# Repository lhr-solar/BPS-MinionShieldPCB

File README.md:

# BPS-MinionShieldPCB
Author: Champers Fu

This board sits on top of the minionshield to interface with the temperature sensors. 
The board provides a low pass filter between the thermistors and the LTC6811 input. 

## BOM
[**Interactive BOM (Must download and open in browser)**](ibom.html)

[**Mouser Cart**](https://www.mouser.com/ProjectManager/ProjectDetail.aspx?AccessID=0a4c326737)
Note: The PADP-24V-1-S connector is not available on mouser, but may be purchased through [**digikey**](https://www.digikey.com/en/products/detail/jst-sales-america-inc/PADP-24V-1-S/1300227)

## Connectors
| Reference | Name | Type | Pin 1 | 2 | 3 | 4 | 5 | 6 | 7 | 8 | 9 | 10 |
| - | - | - | - | - | - | - | - | - | - | - | - | - |
| J1 | MinionPCB Connector | 1x10xP2.54mm Male | 5V | TempSensor1 | TempSensor2 | TempSensor3 | TempSensor4 | TempSensor5 | TempSensor6 | TempSensor7 | TempSensor8 | GND
| J2 | MinionPCB Connector | 1x10xP2.54mm Male | 5V | TempSensor9 | TempSensor10 | TempSensor11 | TempSensor12 | TempSensor13 | TempSensor14 | TempSensor15 | TempSensor16 | GND
| J3 | Thermistors | PADP-24V-1-S | See Schematic | | | | | | | | | |

## PCB
[**PDF without traces**](PCB.pdf)

## Schematic
[**PDF with all sheets**](Schematic.pdf)

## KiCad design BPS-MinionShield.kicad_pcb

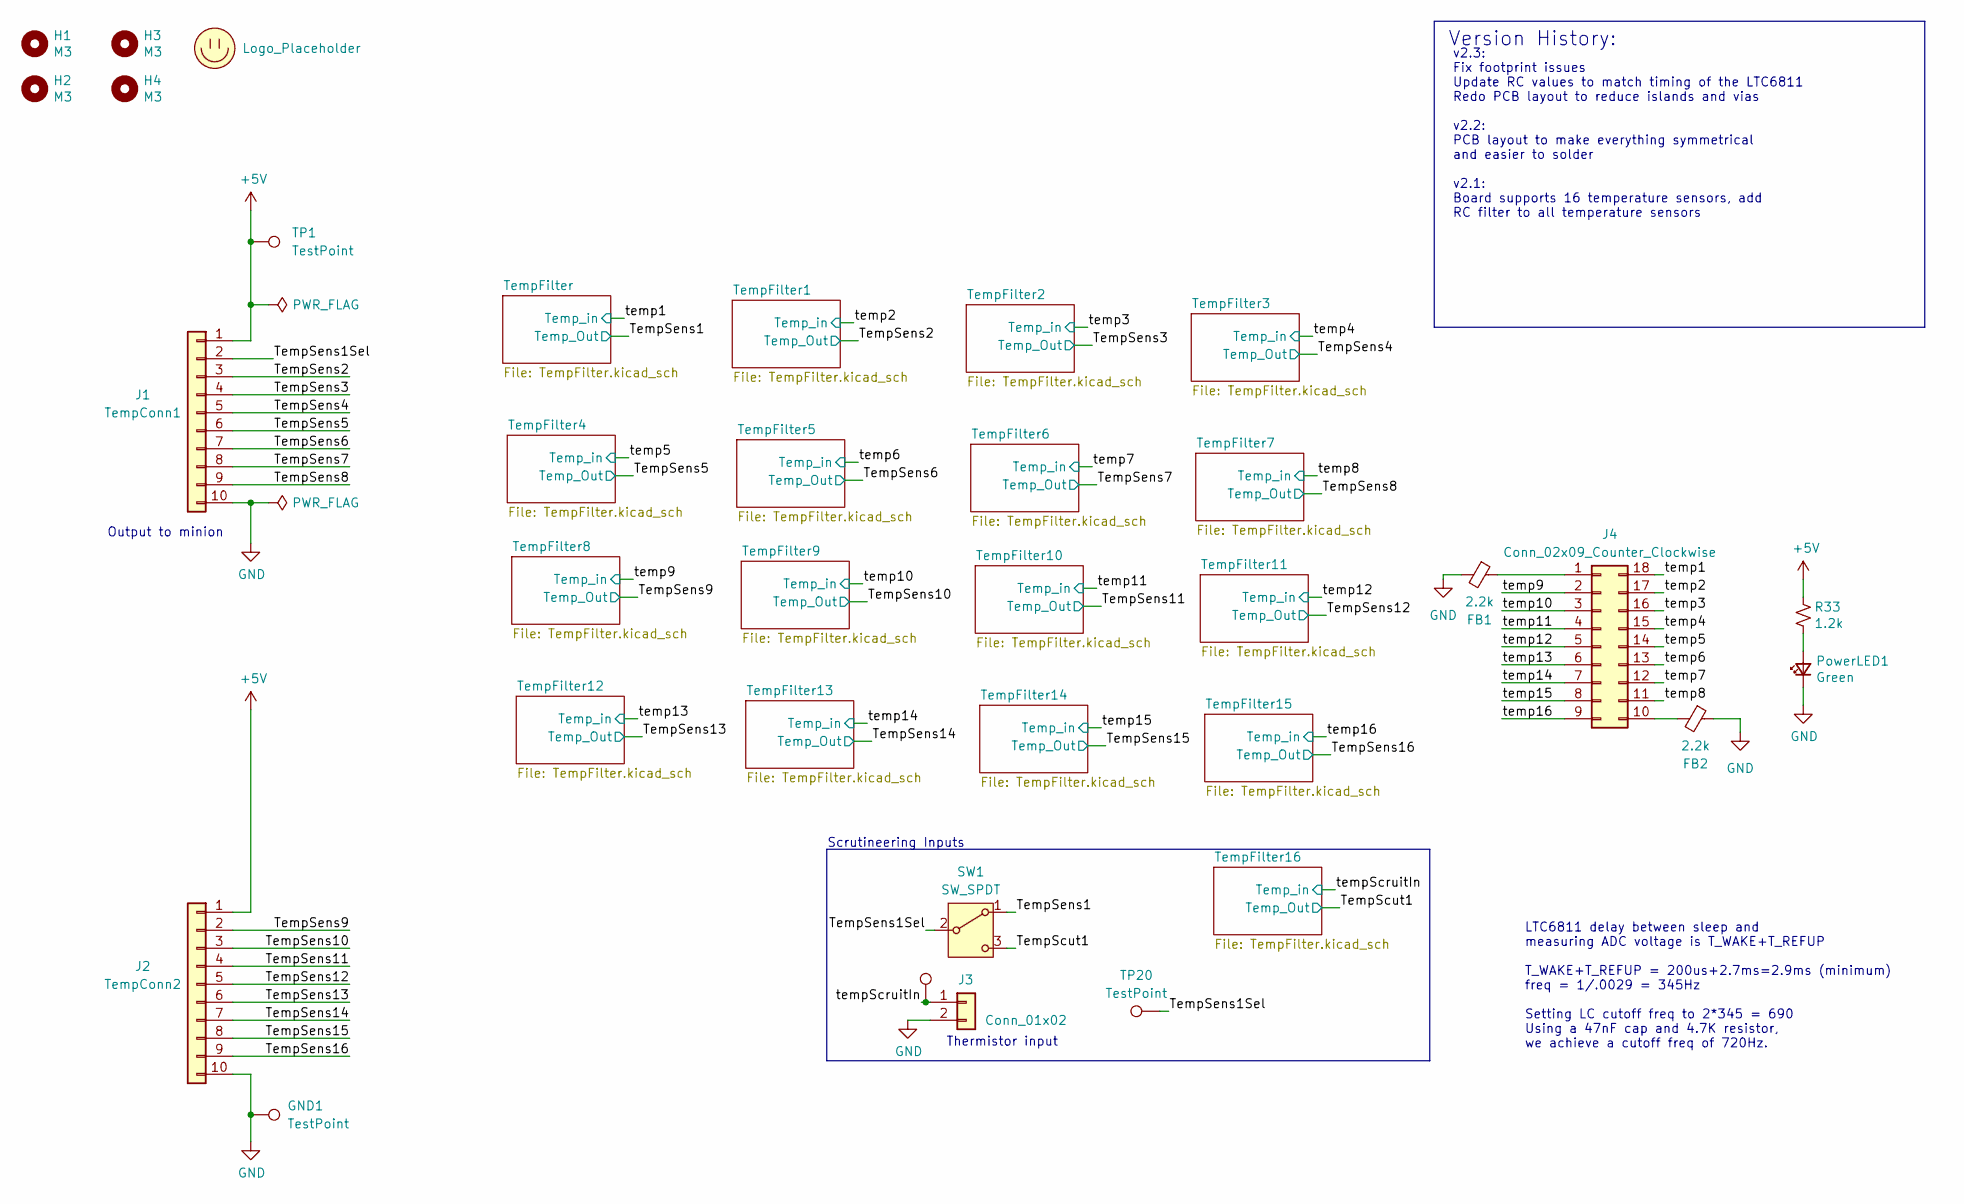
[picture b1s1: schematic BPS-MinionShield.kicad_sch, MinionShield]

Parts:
FB1, FB2: 2.2k; L_0805_2012Metric_Pad1.05x1.20mm_HandSolder
GND1: TestPoint; TestPoint_THTPad_D1.5mm_Drill0.7mm
H1, H2, H3, H4: M3; MountingHole_3mm
J1: TempConn1; PinHeader_1x10_P2.54mm_Vertical
J2: TempConn2; PinHeader_1x10_P2.54mm_Vertical
J3: Conn_01x02; Molex_MicroFit3.0_1x2xP3.00mm_PolarizingPeg_Vertical
J4: Conn_02x09_Counter_Clockwise; Molex_Micro-Fit_3.0_43045-1800_2x09_P3.00mm_Horizontal
LOGO1: Logo_Placeholder; Hallock_Image_Small
PowerLED1: Green; LED_0805_2012Metric_Pad1.15x1.40mm_HandSolder; LCSC Part # C94741
R33: 1.2k; R_0805_2012Metric_Pad1.20x1.40mm_HandSolder; LCSC Part # C17673
SW1: SW_SPDT; CJS1200TB1
TP1, TP2: TestPoint; TestPoint_THTPad_D1.5mm_Drill0.7mm
TP20: TestPoint; TestPoint_Pad_1.5x1.5mm

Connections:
+5V: J1.1, J2.1, R33.1, TP1.1; also elsewhere on the board
/TempScut1: SW1.3 (C); also elsewhere on the board
/TempSens1: SW1.1 (A); also elsewhere on the board
/TempSens1Sel: J1.2, SW1.2 (B), TP20.1
/TempSens2: J1.3; also elsewhere on the board
/TempSens3: J1.4; also elsewhere on the board
/TempSens4: J1.5; also elsewhere on the board
/TempSens5: J1.6; also elsewhere on the board
/TempSens6: J1.7; also elsewhere on the board
/TempSens7: J1.8; also elsewhere on the board
/TempSens8: J1.9; also elsewhere on the board
/TempSens9: J2.2; also elsewhere on the board
/TempSens10: J2.3; also elsewhere on the board
/TempSens11: J2.4; also elsewhere on the board
/TempSens12: J2.5; also elsewhere on the board
/TempSens13: J2.6; also elsewhere on the board
/TempSens14: J2.7; also elsewhere on the board
/TempSens15: J2.8; also elsewhere on the board
/TempSens16: J2.9; also elsewhere on the board
/temp1: J4.18; also elsewhere on the board
/temp2: J4.17; also elsewhere on the board
/temp3: J4.16; also elsewhere on the board
/temp4: J4.15; also elsewhere on the board
/temp5: J4.14; also elsewhere on the board
/temp6: J4.13; also elsewhere on the board
/temp7: J4.12; also elsewhere on the board
/temp8: J4.11; also elsewhere on the board
/temp9: J4.2; also elsewhere on the board
/temp10: J4.3; also elsewhere on the board
/temp11: J4.4; also elsewhere on the board
/temp12: J4.5; also elsewhere on the board
/temp13: J4.6; also elsewhere on the board
/temp14: J4.7; also elsewhere on the board
/temp15: J4.8; also elsewhere on the board
/temp16: J4.9; also elsewhere on the board
/tempScruitIn: J3.1, TP2.1; also elsewhere on the board
GND: FB1.2, FB2.1, GND1.1, J1.10, J2.10, J3.2, PowerLED1.1 (K); also elsewhere on the board
unnamed: FB1.1, J4.1
unnamed: FB2.2, J4.10
unnamed: PowerLED1.2 (A), R33.2

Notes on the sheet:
Thermistor input
Version History:
v2.3: Fix footprint issues Update RC values to match timing of the LTC6811 Redo PCB layout to reduce islands and vias v2.2: PCB layout to make everything symmetrical and easier to solder v2.1: Board supports 16 temperature sensors, add RC filter to all temperature sensors
Scrutineering Inputs
LTC6811 delay between sleep and measuring ADC voltage is T_WAKE+T_REFUP T_WAKE+T_REFUP = 200us+2.7ms=2.9ms (minimum) freq = 1/.0029 = 345Hz Setting LC cutoff freq to 2*345 = 690 Using a 47nF cap and 4.7K resistor, we achieve a cutoff freq of 720Hz.
Output to minion

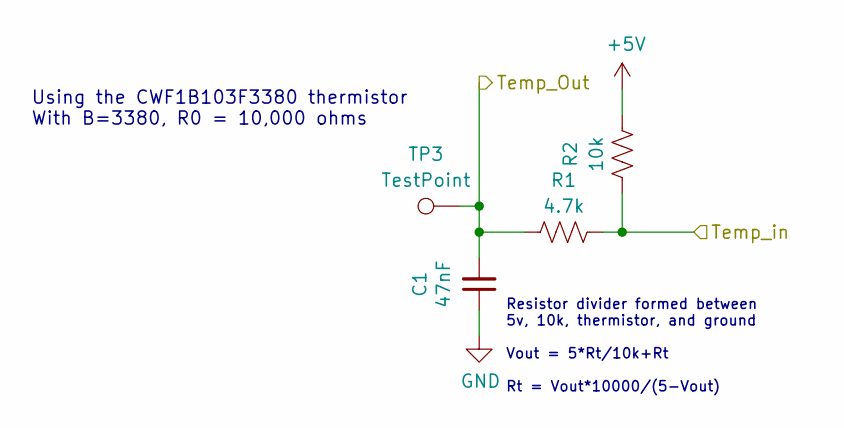
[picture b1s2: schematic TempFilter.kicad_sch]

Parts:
C1: 47nF; C_0805_2012Metric_Pad1.18x1.45mm_HandSolder; LCSC Part # C1745
R1: 4.7k; R_0805_2012Metric_Pad1.20x1.40mm_HandSolder; LCSC Part # C17673
R2: 10k; R_0805_2012Metric_Pad1.20x1.40mm_HandSolder; LCSC Part # C17414
TP3: TestPoint; TestPoint_Pad_1.5x1.5mm

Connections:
+5V: R2.2; also elsewhere on the board
/TempSens1: C1.2, R1.1, TP3.1; also elsewhere on the board
/temp1: R1.2, R2.1; also elsewhere on the board
GND: C1.1; also elsewhere on the board

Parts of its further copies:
C2, C3, C4, C5, C6, C7, C8, C9, C10, C11, C12, C13, C14, C15, C16, C17: 47nF; C_0805_2012Metric_Pad1.18x1.45mm_HandSolder; LCSC Part # C1745
R3, R5, R7, R9, R11, R13, R15, R17, R19, R21, R23, R25, R27, R29, R31, R34: 4.7k; R_0805_2012Metric_Pad1.20x1.40mm_HandSolder; LCSC Part # C17673
R4, R6, R8, R10, R12, R14, R16, R18, R20, R22, R24, R26, R28, R30, R32, R35: 10k; R_0805_2012Metric_Pad1.20x1.40mm_HandSolder; LCSC Part # C17414
TP4, TP5, TP6, TP7, TP8, TP9, TP10, TP11, TP12, TP13, TP14, TP15, TP16, TP17, TP18, TP19: TestPoint; TestPoint_Pad_1.5x1.5mm

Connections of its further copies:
+5V: R4.2, R6.2, R8.2, R10.2, R12.2, R14.2, R16.2, R18.2, R20.2, R22.2, R24.2, R26.2, R28.2, R30.2, R32.2, R35.2; also elsewhere on the board
/TempScut1: C17.2, R34.1, TP19.1; also elsewhere on the board
/TempSens2: C2.2, R3.1, TP4.1; also elsewhere on the board
/TempSens3: C3.2, R5.1, TP5.1; also elsewhere on the board
/TempSens4: C4.2, R7.1, TP6.1; also elsewhere on the board
/TempSens5: C5.2, R9.1, TP7.1; also elsewhere on the board
/TempSens6: C6.2, R11.1, TP8.1; also elsewhere on the board
/TempSens7: C7.2, R13.1, TP9.1; also elsewhere on the board
/TempSens8: C8.2, R15.1, TP10.1; also elsewhere on the board
/TempSens9: C9.2, R17.1, TP11.1; also elsewhere on the board
/TempSens10: C10.2, R19.1, TP12.1; also elsewhere on the board
/TempSens11: C11.2, R21.1, TP13.1; also elsewhere on the board
/TempSens12: C12.2, R23.1, TP14.1; also elsewhere on the board
/TempSens13: C13.2, R25.1, TP15.1; also elsewhere on the board
/TempSens14: C14.2, R27.1, TP16.1; also elsewhere on the board
/TempSens15: C15.2, R29.1, TP17.1; also elsewhere on the board
/TempSens16: C16.2, R31.1, TP18.1; also elsewhere on the board
/temp2: R3.2, R4.1; also elsewhere on the board
/temp3: R5.2, R6.1; also elsewhere on the board
/temp4: R7.2, R8.1; also elsewhere on the board
/temp5: R9.2, R10.1; also elsewhere on the board
/temp6: R11.2, R12.1; also elsewhere on the board
/temp7: R13.2, R14.1; also elsewhere on the board
/temp8: R15.2, R16.1; also elsewhere on the board
/temp9: R17.2, R18.1; also elsewhere on the board
/temp10: R19.2, R20.1; also elsewhere on the board
/temp11: R21.2, R22.1; also elsewhere on the board
/temp12: R23.2, R24.1; also elsewhere on the board
/temp13: R25.2, R26.1; also elsewhere on the board
/temp14: R27.2, R28.1; also elsewhere on the board
/temp15: R29.2, R30.1; also elsewhere on the board
/temp16: R31.2, R32.1; also elsewhere on the board
/tempScruitIn: R34.2, R35.1; also elsewhere on the board
GND: C2.1, C3.1, C4.1, C5.1, C6.1, C7.1, C8.1, C9.1, C10.1, C11.1, C12.1, C13.1, C14.1, C15.1, C16.1, C17.1; also elsewhere on the board

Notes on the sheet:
Using the CWF1B103F3380 thermistor With B=3380, R0 = 10,000 ohms
Resistor divider formed between 5v, 10k, thermistor, and ground Vout = 5*Rt/10k+Rt Rt = Vout*10000/(5-Vout)

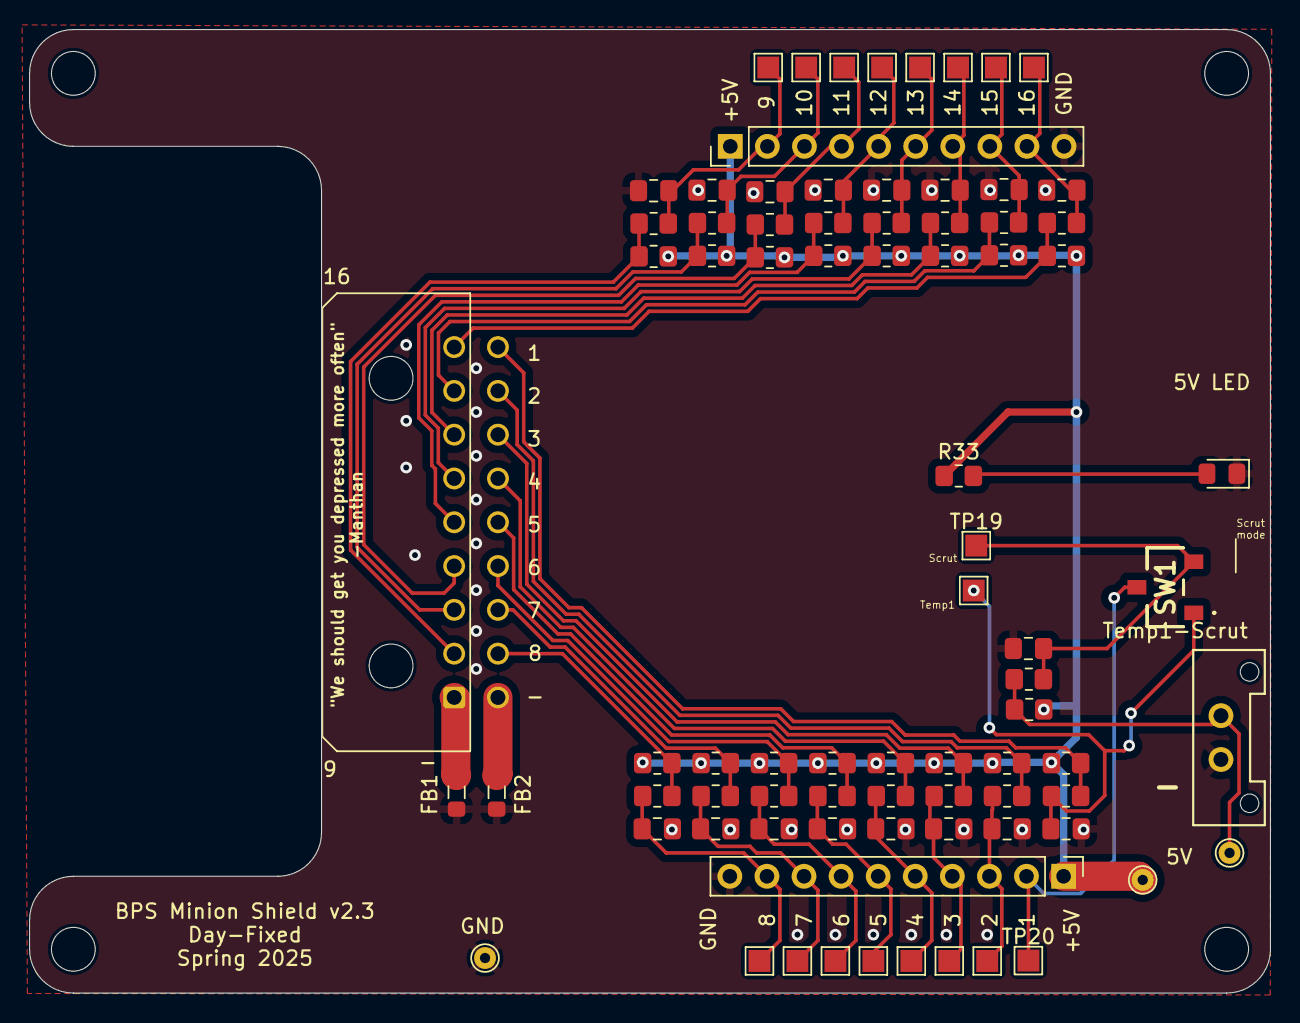
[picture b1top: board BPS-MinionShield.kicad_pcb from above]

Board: 2 copper layers, 85.0 x 66.0 mm, 86 parts (1 on the bottom side), 40 nets.

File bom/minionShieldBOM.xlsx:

Reference | Value | Datasheet | Footprint | Qty | DNP | p/n
C1,C2,C3,C4,C5,C6,C7,C8,C9,C10,C11,C12,C13,C14,C15,C16 | 47nF | https://www.mouser.com/ProductDetail/YAGEO/CC0805JRX7R9BB473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 | Capacitor_SMD:C_0805_2012Metric_Pad1.18x1.45mm_HandSolder | 16 |  | CC0805JRX7R9BB473
FB1,FB2 | 2.2k | https://www.digikey.com/en/products/detail/laird-signal-inte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 | Inductor_SMD:L_0805_2012Metric_Pad1.05x1.20mm_HandSolder | 2 |  | HZ0805B222R-10
J3 | Conn_01x02 | ~ | UTSVT_Connectors:Molex_MicroFit3.0_1x2xP3.00mm_PolarizingPeg_Vertical | 1 |  | 436500227
J4 | Conn_02x09_Counter_Clockwise | ~ | Connector_Molex:Molex_Micro-Fit_3.0_43045-1800_2x09_P3.00mm_Horizontal | 1 |  | 43045-1800
PowerLED1 | Green | https://www.mouser.com/ProductDetail/710-150080VS75000 | LED_SMD:LED_0805_2012Metric_Pad1.15x1.40mm_HandSolder | 1 |  | 150080VS75000
R1,R3,R5,R7,R9,R11,R13,R15,R17,R19,R21,R23,R25,R27,R29,R31 | 4.7k | https://www.mouser.com/ProductDetail/603-RT0805FRE074K7L | Resistor_SMD:R_0805_2012Metric_Pad1.20x1.40mm_HandSolder | 16 |  | RT0805FRE074K7L
R2,R4,R6,R8,R10,R12,R14,R16,R18,R20,R22,R24,R26,R28,R30,R32 | 10k | https://www.mouser.com/ProductDetail/603-RT0805FRE0710KL | Resistor_SMD:R_0805_2012Metric_Pad1.20x1.40mm_HandSolder | 16 |  | RT0805FRE0710KL
R33 | 1.2k | https://www.mouser.com/ProductDetail/603-RT0805FRE071K2L | Resistor_SMD:R_0805_2012Metric_Pad1.20x1.40mm_HandSolder | 1 |  | RT0805FRE071K2L
SW1 | SW_DIP_x01 | ~ | MinionShield:DS04254201BKSMT | 1 |  | DS04-254-2-01BK-SMT

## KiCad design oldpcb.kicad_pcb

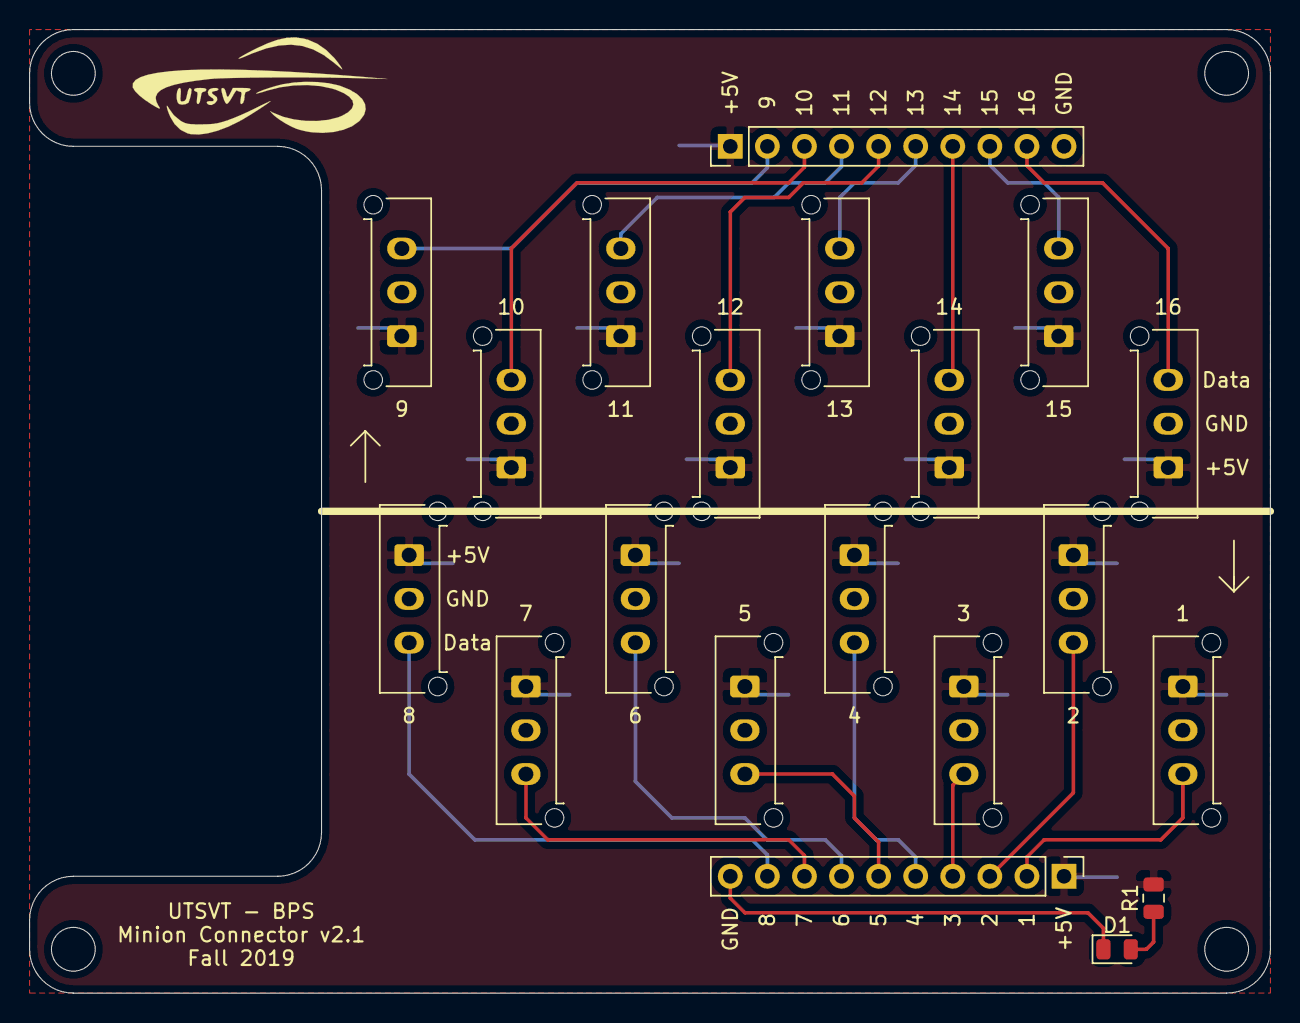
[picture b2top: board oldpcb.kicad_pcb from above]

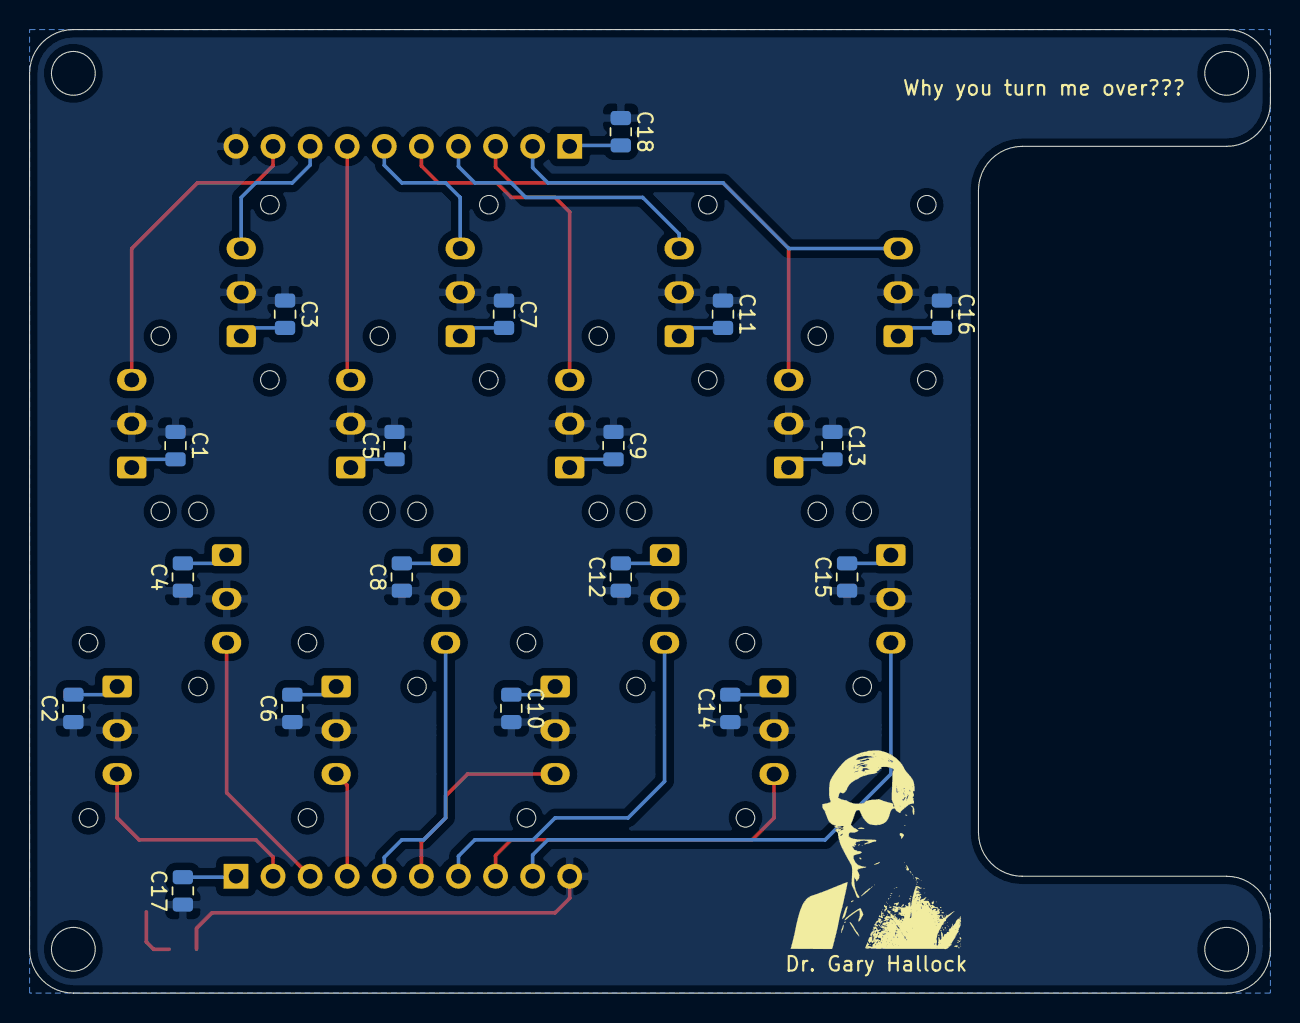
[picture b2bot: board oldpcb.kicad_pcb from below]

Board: 2 copper layers, 85.0 x 66.0 mm, 42 parts (18 on the bottom side), 19 nets.

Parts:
C1, C2, C3, C4, C5, C6, C7, C8, C9, C10, C11, C12, C13, C14, C15, C16, C17, C18: 100n; C_0805_2012Metric
D1: Green; LED_0805_2012Metric
H1, H2, H3, H4: M3; MountingHole_3mm
J1: TempConn2; Molex_Micro-Fit_3.0_43650-0315_1x03_P3.00mm_Vertical
J2: TempConn3; Molex_Micro-Fit_3.0_43650-0315_1x03_P3.00mm_Vertical
J3: TempConn4; Molex_Micro-Fit_3.0_43650-0315_1x03_P3.00mm_Vertical
J4: TempConn5; Molex_Micro-Fit_3.0_43650-0315_1x03_P3.00mm_Vertical
J5: TempConn6; Molex_Micro-Fit_3.0_43650-0315_1x03_P3.00mm_Vertical
J6: TempConn7; Molex_Micro-Fit_3.0_43650-0315_1x03_P3.00mm_Vertical
J7: TempConn1; Molex_Micro-Fit_3.0_43650-0315_1x03_P3.00mm_Vertical
J8: TempConn8; Molex_Micro-Fit_3.0_43650-0315_1x03_P3.00mm_Vertical
J9, J14: TempConn2; PinHeader_1x10_P2.54mm_Vertical
J10: TempConn9; Molex_Micro-Fit_3.0_43650-0315_1x03_P3.00mm_Vertical
J11: TempConn10; Molex_Micro-Fit_3.0_43650-0315_1x03_P3.00mm_Vertical
J12: TempConn11; Molex_Micro-Fit_3.0_43650-0315_1x03_P3.00mm_Vertical
J13: TempConn12; Molex_Micro-Fit_3.0_43650-0315_1x03_P3.00mm_Vertical
J15: TempConn13; Molex_Micro-Fit_3.0_43650-0315_1x03_P3.00mm_Vertical
J16: TempConn14; Molex_Micro-Fit_3.0_43650-0315_1x03_P3.00mm_Vertical
J17: TempConn15; Molex_Micro-Fit_3.0_43650-0315_1x03_P3.00mm_Vertical
J18: TempConn16; Molex_Micro-Fit_3.0_43650-0315_1x03_P3.00mm_Vertical
R1: 1.2k; R_0805_2012Metric

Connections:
+5V: C1.2, C2.2, C3.2, C4.2, C5.1, C6.2, C7.2, C8.2, C9.2, C10.1, C11.2, C12.2, C13.2, C14.2, C15.2, C16.2, C17.2, C18.2, J1.1, J2.1, J3.1, J4.1, J5.1, J6.1, J7.1, J8.1, J9.1, J10.1, J11.1, J12.1, J13.1, J14.1, J15.1, J16.1, J17.1, J18.1, R1.1
/TempSens1: J7.3, J9.2
/TempSens2: J1.3, J9.3
/TempSens3: J2.3, J9.4
/TempSens4: J3.3, J9.5
/TempSens5: J4.3, J9.6
/TempSens6: J5.3, J9.7
/TempSens7: J6.3, J9.8
/TempSens8: J8.3, J9.9
/TempSens9: J10.3, J14.2
/TempSens10: J11.3, J14.3
/TempSens11: J12.3, J14.4
/TempSens12: J13.3, J14.5
/TempSens13: J14.6, J15.3
/TempSens14: J14.7, J16.3
/TempSens15: J14.8, J17.3
/TempSens16: J14.9, J18.3
GND: C1.1, C2.1, C3.1, C4.1, C5.2, C6.1, C7.1, C8.1, C9.1, C10.2, C11.1, C12.1, C13.1, C14.1, C15.1, C16.1, C17.1, C18.1, D1.1, J1.2, J2.2, J3.2, J4.2, J5.2, J6.2, J7.2, J8.2, J9.10, J10.2, J11.2, J12.2, J13.2, J14.10, J15.2, J16.2, J17.2, J18.2
unnamed: D1.2, R1.2

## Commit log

2020-08-16 Adds BPS Minion Shield kicad project
2020-08-16 Adds documentation files and submodules
2020-08-16 Adds mouser cart in readme
2020-09-01 Renames project to not include PCB
2020-10-03 Adds QuAC
2022-09-23 Added RC filter to all temperature sensors
2022-09-24 added ferrite beads, datasheets, and footprints
2022-09-26 made capacitors pretty
2022-10-01 generated bom
2022-10-01 added thermistor detail
2022-10-08 added tvs diodes
2022-10-16 finished PCB layout with a displayport connector for thermistors
2022-10-22 added orion connector footprint
2022-10-29 new footprint from temp expansion module
2022-11-05 pcb routing done
2022-11-12 made stuff pretty and rerouted
2022-11-19 redid the vias
2022-11-28 rerouted and added Dr. Hallock photo
2022-12-03 generated mouser cart and gerber files
2022-12-03 actually added gerber files
2022-12-03 removed some gnd test points
2022-12-07 implemented hannah changes and added personalization
2022-12-16 keep just 1 gnd testpoint
2022-12-26 fix connector footprint, change quotes
2023-01-21 add PADP-24 connector to submodule
2023-01-21 fix footprints and reference designators
2023-01-21 update pdfs
2023-01-22 update mouser cart
2023-01-25 update connector from digikey
2023-02-06 change to all passives to 0805 footprints
2023-02-25 update quac
2023-02-25 move ferrite beads for more space
2023-02-25 Revert "update connector from digikey"
    This reverts commit 7205807fa5bedf384e424ba98877d198a6dc1d85.
2023-02-25 Revert "move ferrite beads for more space"
    This reverts commit 10398d522d6bd349285b691c333d995223f13479.
2023-02-27 move ferrite beads away from connector
2023-02-27 update qac
2023-03-04 fix gitignore
2023-03-04 remove backups
2023-05-19 fix some islands
2023-05-19 change cap values to 100nf
2023-05-21 address maestro tianda's review
2023-05-21 Standardized common repo, added version history, updated readme, added board models
2023-05-21 renamed files
2023-05-22 Added BOM
2023-05-22 set common and bps-libs to master
2023-05-22 Updated pull request template
2023-05-22 Added 3D model and updated version history
2023-05-22 Added 3D model from libraries to pcb
2023-05-22 remove unused lib
2023-05-25 address all tianda requests, start standardization
2023-05-28 Added excel BOM and updated readme with mouser cart
2023-05-29 Changed BOM to fix resistor labels
2023-05-29 removed BPS-libs
2023-06-04 address manthan changes, finalize PR
2023-06-05 fix readme
2023-06-05 fix table
2023-06-06 fix table again
2023-06-06 make vias more pretty
2023-09-23 Added zip files
2023-11-15 Fixed gerbers
2025-03-07 started reworking hat
2025-03-08 fucckkkkk
2025-03-08 board done
2025-03-09 step files
2025-03-16 update for standardization
2025-03-17 move to minion shield
2025-03-18 testing with new library
2025-03-19 yipee
2025-05-31 shrug
